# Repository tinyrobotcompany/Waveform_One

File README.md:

# Waveform One

A music-reactive LED display using an ESP32-S3, INMP441 microphone and 64×32
HUB75 panel. The current working prototype connects the panel directly to the
ESP32-S3. The ESP32-P4 touchscreen controller selects visual styles over USB,
joins the user's home Wi-Fi and hosts the local phone remote.

Migration to the Waveshare ESP32-P4-WIFI6-Touch-LCD-7B display controller is
under development. Display, touch, home Wi-Fi setup, the phone remote and S3
style control are working. Native music recognition has host/reference
verification and awaits physical P4 acceptance. The working
ESP32-S3 audio and HUB75 engine remains intact during this migration.

- [Wiring, firmware programs and build instructions](firmware/esp32/README.md)
- [ESP32-P4 display bring-up and wiring](firmware/esp32/p4_display/README.md)
- [ESP32-P4 controller architecture decision](docs/architecture/0001-esp32-p4-display-controller.md)
- [Contributing and local tests](CONTRIBUTING.md)
- [Release notes](CHANGELOG.md)
- [Over-the-air updates: development and production](pi/updater/README.md)
- [CI and releases](docs/delivery.md)
- [Pi setup and visual-style controls](pi/README.md)

Signed releases support Pi application and ESP firmware updates on commissioned devices.
Development devices install automatically; production devices ask the user to install.
Existing factory-layout ESP boards need a one-time USB migration before OTA updates.

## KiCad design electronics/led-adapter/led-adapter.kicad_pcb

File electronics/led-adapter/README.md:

# LED adapter board

A small board (72 × 44 mm) that connects the P4 touchscreen board to the LED
panel, so the P4 can drive the panel without the ESP32-S3 and without loose
jumper wires. Every cable plugs in at both ends.

```text
P4 socket P3 ──[PH2.0 12-pin cable]── J1 ┐
                                         ├─ buffers ── J3 ──[panel's grey ribbon]── LED panel
P4 socket P1 ──[PH2.0 12-pin cable]── J2 ┘
                       5 V from the LED supply ── J4
```

| Connector | Takes |
|---|---|
| J1 | Cable to the P4's **P3** socket (GPIO2–5, 28–31, 34; 3.3 V and GND) |
| J2 | Cable to the P4's **P1** socket (GPIO49–52; GND) |
| J3 | The LED panel's own 16-pin ribbon (HUB75) |
| J4 | 5 V and GND from the LED panel's supply (screw terminal) |

The labels are printed on the board.

## In the case

The board lies flat on four floor posts (M3 heat-set inserts, 5 mm high) in
the left half, behind the screen and under the P4's two 12-pin sockets, with
J1 and J2 towards the back. `board.json` gives its position (`case_left_x`,
`case_rear_y`, `standoff_height`); the casing CAD reads it from
`placement.json`, as it does for the carrier board.

## What is on it

- **Two 74AHCT245 buffers** turn the P4's 3.3 V signals into the 5 V the
  panel expects. These are the same buffers as on the carrier board.
- **The panel stays dark unless the P4 is on.** Q1 enables the buffers only
  while the P4's 3.3 V is present. Otherwise R4 holds the panel's OE high.
  R1 does the same while the P4 starts.
- **5 V comes from the LED panel's supply** through J4. The buffers draw only
  a few mA, and the P4's 12-pin sockets carry no 5 V.

The signal map is Codex's, from
`docs/commissioning/2026-10-14-p4-led-takeover.md`:

| HUB75 | R1 | G1 | B1 | R2 | G2 | B2 | A | B | C | D | CLK | LAT | OE |
|---|---|---|---|---|---|---|---|---|---|---|---|---|---|
| P4 GPIO | 2 | 3 | 4 | 5 | 28 | 29 | 30 | 31 | 34 | 49 | 52 | 50 | 51 |

The P4's socket pins come from Waveshare's 7B schematic (P1 and P3).
`tools/netlist.py` lists them pin by pin.

## Cables to buy

- **2 × PH2.0 12-pin cables with a plug at both ends, "same direction"**
  (sometimes listed as 同向 or "forward"). 10–15 cm long.
  - "Same direction" means wire 1 goes to pin 1 at the other end. The
    "reverse" kind sends wire 1 to pin 12 and **will not work**.
  - Before plugging one in, check with a multimeter that the end wires meet the
    same-numbered pins.
- The panel's grey 16-pin ribbon, which came with the panel.
- Two short wires (red and black) from the LED supply's screw terminal to J4.

## Order from JLCPCB

```sh
python3 electronics/led-adapter/tools/export_jlc.py
```

This writes `fab/`. On jlcpcb.com, follow the carrier board's steps
(`electronics/carrier/README.md`, "Order from JLCPCB"):

1. Upload `led-adapter-gerbers.zip`. Use the defaults: 2 layers, 1.6 mm,
   quantity 5.
2. Turn on PCB Assembly, top side. J1–J4 are through-hole, so choose
   **Standard** assembly with through-hole soldering.
3. Upload `led-adapter-bom.csv` and `led-adapter-cpl.csv`. Check that every
   part is matched and in stock.
4. In the placement preview, check that each part sits the right way round.
   Compare it with KiCad's render (`kicad-cli pcb render --side top`):
   - pin 1 of U1, U2, Q1, J1, J2 and J3;
   - the wire entries of J4, which face the board's front edge (away from the
     "+5V" and "GND" text), so the wires come in from the front as the case
     expects.

   Rotate any part that is wrong in JLCPCB's preview. Revision 1 was ordered
   with J4 turned the other way, and JLCPCB was asked to turn it 180° (2026-10-20);
   these files now have it the right way round.

## Regenerate

The tools reuse the carrier board's generators (`reuse.py` points them at this
folder). Don't edit the generated files by hand. Edit `tools/netlist.py` or
`board.json` instead, then run:

```sh
python3 electronics/led-adapter/tools/gen_schematic.py
KP=/Applications/KiCad/KiCad.app/Contents/Frameworks/Python.framework/Versions/Current/bin/python3
$KP electronics/led-adapter/tools/build_board.py
$KP electronics/led-adapter/tools/route_board.py      # needs Java and Freerouting, as for the carrier
K=/Applications/KiCad/KiCad.app/Contents/MacOS/kicad-cli
$K sch erc electronics/led-adapter/led-adapter.kicad_sch
$K pcb drc --schematic-parity electronics/led-adapter/led-adapter.kicad_pcb
```

## Status

- Designed, routed and checked: no design-rule violations, nothing
  unconnected, and the board matches the schematic.
- **Not yet ordered.**
- Order it only after the jumper bench test shows the panel works from the P4
  with this signal map.

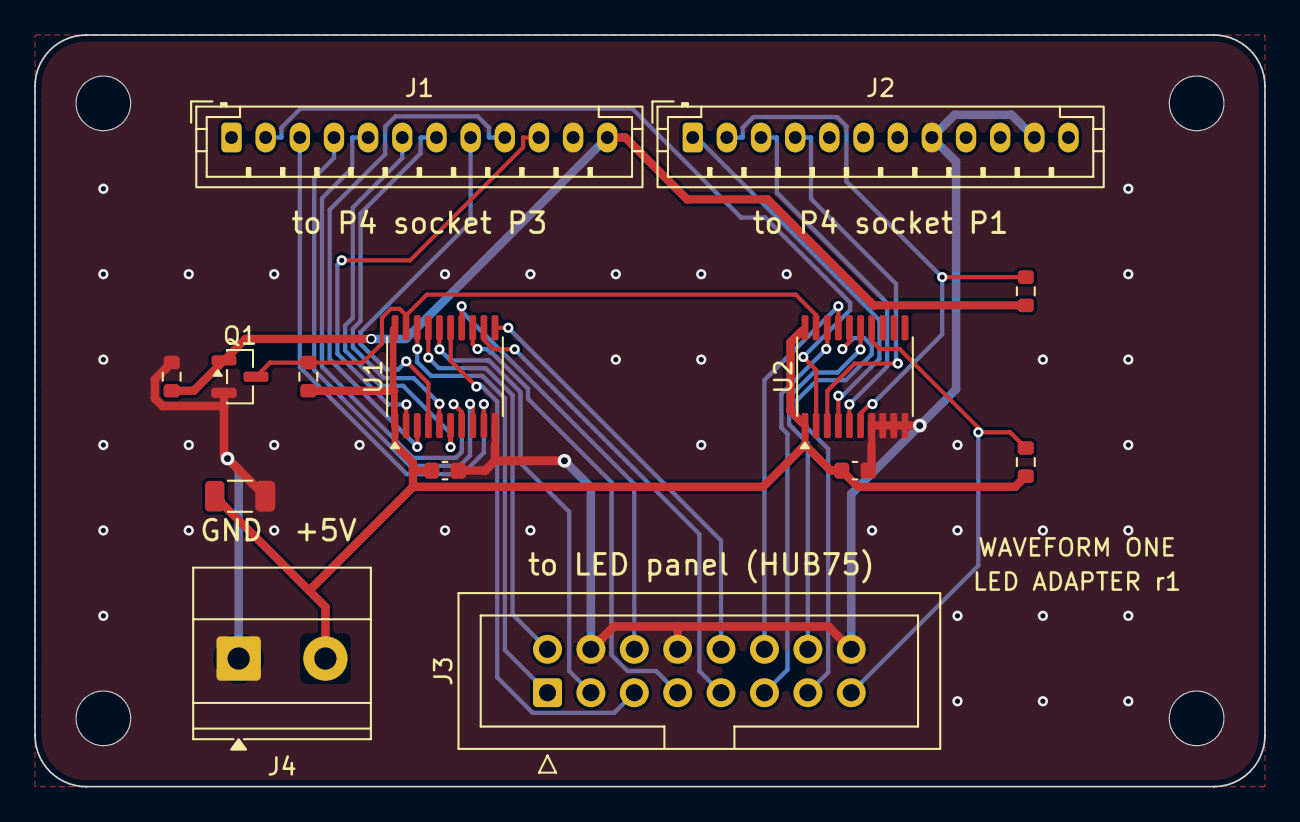
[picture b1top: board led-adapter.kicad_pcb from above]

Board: 2 copper layers, 72.0 x 44.0 mm, 18 parts (0 on the bottom side), 30 nets.

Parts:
C1, C2: 100nF; C_0603_1608Metric
C3: 22uF 10V; C_1206_3216Metric
H1, H2, H3, H4: M3; MountingHole_3.2mm_M3
J1, J2: PH2.0 12-pin; JST_PH_B12B-PH-K_1x12_P2.00mm_Vertical
J3: HUB75; IDC-Header_2x08_P2.54mm_Vertical
J4: 5V in; TerminalBlock_Phoenix_MKDS-1,5-2-5.08_1x02_P5.08mm_Horizont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
Q1: 2N7002; SOT-23
R1, R3, R4: 10k; R_0603_1608Metric
R2: 100k; R_0603_1608Metric
U1, U2: 74AHCT245; TSSOP-20_4.4x6.5mm_P0.65mm

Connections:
/+5V: C1.1, C2.1, C3.1, J4.2, R3.1, R4.1, U1.1, U1.20, U2.1, U2.20
/BUF_EN: Q1.3, R3.2, U1.19, U2.19
/GND: C1.2, C2.2, C3.2, J1.11, J2.8, J2.11, J3.4, J3.8, J3.16, J4.1, Q1.2, R2.2, U1.10, U2.7, U2.8, U2.9, U2.10
/HUB_A: J3.9, U1.12
/HUB_B: J3.10, U1.11
/HUB_B1: J3.3, U1.16
/HUB_B2: J3.7, U1.13
/HUB_C: J3.11, U2.18
/HUB_CLK: J3.13, U2.16
/HUB_D: J3.12, U2.17
/HUB_G1: J3.2, U1.17
/HUB_G2: J3.6, U1.14
/HUB_LAT: J3.14, U2.15
/HUB_OE: J3.15, R4.2, U2.14
/HUB_R1: J3.1, U1.18
/HUB_R2: J3.5, U1.15
/P4_3V3: J1.12, Q1.1, R1.1, R2.1
/P4_A: J1.4, U1.8
/P4_B: J1.3, U1.9
/P4_B1: J1.8, U1.4
/P4_B2: J1.5, U1.7
/P4_C: J1.2, U2.2
/P4_CLK: J2.1, U2.4
/P4_D: J2.4, U2.3
/P4_G1: J1.9, U1.3
/P4_G2: J1.6, U1.6
/P4_LAT: J2.3, U2.5
/P4_OE: J2.2, R1.2, U2.6
/P4_R1: J1.10, U1.2
/P4_R2: J1.7, U1.5

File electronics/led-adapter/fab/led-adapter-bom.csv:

Comment,Designator,Footprint,LCSC Part #
PH2.0 12-pin,"J1,J2",JST_PH_B12B-PH-K_1x12_P2.00mm_Vertical,C158028
10k,"R1,R3,R4",R_0603_1608Metric,C25804
2N7002,Q1,SOT-23,C8545
100k,R2,R_0603_1608Metric,C25803
74AHCT245,"U1,U2",TSSOP-20_4.4x6.5mm_P0.65mm,C173388
100nF,"C1,C2",C_0603_1608Metric,C14663
HUB75,J3,IDC-Header_2x08_P2.54mm_Vertical,C492443
5V in,J4,"TerminalBlock_Phoenix_MKDS-1,5-2-5.08_1x02_P5.08mm_Horizontal",C480516
22uF 10V,C3,C_1206_3216Metric,C12891

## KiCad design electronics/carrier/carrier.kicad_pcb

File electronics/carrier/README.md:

# Carrier board

The board inside the cabinet that carries the ESP32-S3, drives the LED panel,
connects the microphone and shares out power. See [SPEC.md](SPEC.md).

Designed in KiCad 10. Placement is generated from `board.json`, which is the
single source for the outline, mounting holes and connector positions. The
casing CAD reads the same file.

## Rebuild the board placement

```sh
/Applications/KiCad/KiCad.app/Contents/Frameworks/Python.framework/Versions/Current/bin/python3 \
    electronics/carrier/tools/build_board.py
```

## Route

```sh
/Applications/KiCad/KiCad.app/Contents/Frameworks/Python.framework/Versions/Current/bin/python3 \
    electronics/carrier/tools/route_board.py
```

Needs Java and Freerouting 2.4.1 (`FREEROUTING_JAR`). It replaces all copper:
it draws the fixed tracks in `route_board.py`, autoroutes the rest, pours
ground and stitches it, and reports what is left unconnected. Rerun it after
every `build_board.py`.

## Order from JLCPCB

```sh
python3 electronics/carrier/tools/export_jlc.py
```

This writes `fab/`: `carrier-gerbers.zip` (the board), `carrier-bom.csv`
(parts with LCSC numbers, from `LCSC` in `netlist.py`) and `carrier-cpl.csv`
(part positions). Not-fitted parts are left out. On jlcpcb.com:

1. Upload `carrier-gerbers.zip`. Keep the defaults: 2 layers, 1.6 mm,
   1 oz copper, HASL lead-free (or ENIG), quantity 5.
2. Turn on PCB Assembly: top side, assemble 5 boards. The through-hole
   connectors (J1, J4, J5, J6) need Standard assembly with through-hole
   soldering, not Economic.
3. Upload `carrier-bom.csv` and `carrier-cpl.csv`. Check every part is
   matched and in stock.
4. In the placement preview, check each polarised part sits the right way
   round: pin 1 of U1, U4, U5, U6, U7 and J7; the stripe of D1; the green LED
   D2; the + of C1; and that each connector faces the board edge it should.
   JLCPCB's part models can be rotated from KiCad's; rotate any that are
   wrong there.

## Check and preview

```sh
K=/Applications/KiCad/KiCad.app/Contents/MacOS/kicad-cli
$K pcb drc --severity-all -o /tmp/carrier-drc.txt electronics/carrier/carrier.kicad_pcb
$K pcb render --side top -o /tmp/carrier-top.png electronics/carrier/carrier.kicad_pcb
```

## Design source

`tools/netlist.py` holds the circuit: every part, value, footprint and pin net.
Two generators read it:

- `tools/gen_schematic.py` writes `carrier.kicad_sch`. Any Python 3.9+ runs it.
- `tools/build_board.py` writes `carrier.kicad_pcb`, with every pad on its net,
  and `placement.json`. It needs KiCad's Python.

Do not edit the generated files by hand. Change `netlist.py`, `board.json` or
the fixed copper in `route_board.py` and regenerate:

```sh
python3 electronics/carrier/tools/gen_schematic.py
KP=/Applications/KiCad/KiCad.app/Contents/Frameworks/Python.framework/Versions/Current/bin/python3
$KP electronics/carrier/tools/build_board.py
$KP electronics/carrier/tools/route_board.py
K=/Applications/KiCad/KiCad.app/Contents/MacOS/kicad-cli
$K sch erc electronics/carrier/carrier.kicad_sch
$K pcb drc --schematic-parity electronics/carrier/carrier.kicad_pcb
```

## Status

Revision 1 is placed and routed.

- Schematic: passes the electrical rules check. The only warnings are the
  three intentional ties of unused buffer inputs to ground.
- Board: matches the schematic exactly, and passes the design-rule check with
  no errors and nothing unconnected. Four warnings remain: the silkscreen
  outlines of the USB-A socket (J4) and the LED power terminal (J6) overhang
  the board edge, as those connectors do by design. A fifth flags that the
  S3 module's footprint differs from KiCad's library: its ground-pad holes
  are drilled 0.3 mm instead of 0.2 mm, so every hole on the board is a
  standard drill size at JLCPCB.
- Chip resistor and capacitor references are left off the silkscreen (too
  dense); they remain on the fabrication layer.
- The USB-C power parts are marked do-not-populate. Their layout is complete
  but provisional; see SPEC.md before fitting them.

Library warnings in `kicad-cli` mean KiCad's global library tables are not set
up yet. Opening KiCad once creates them.

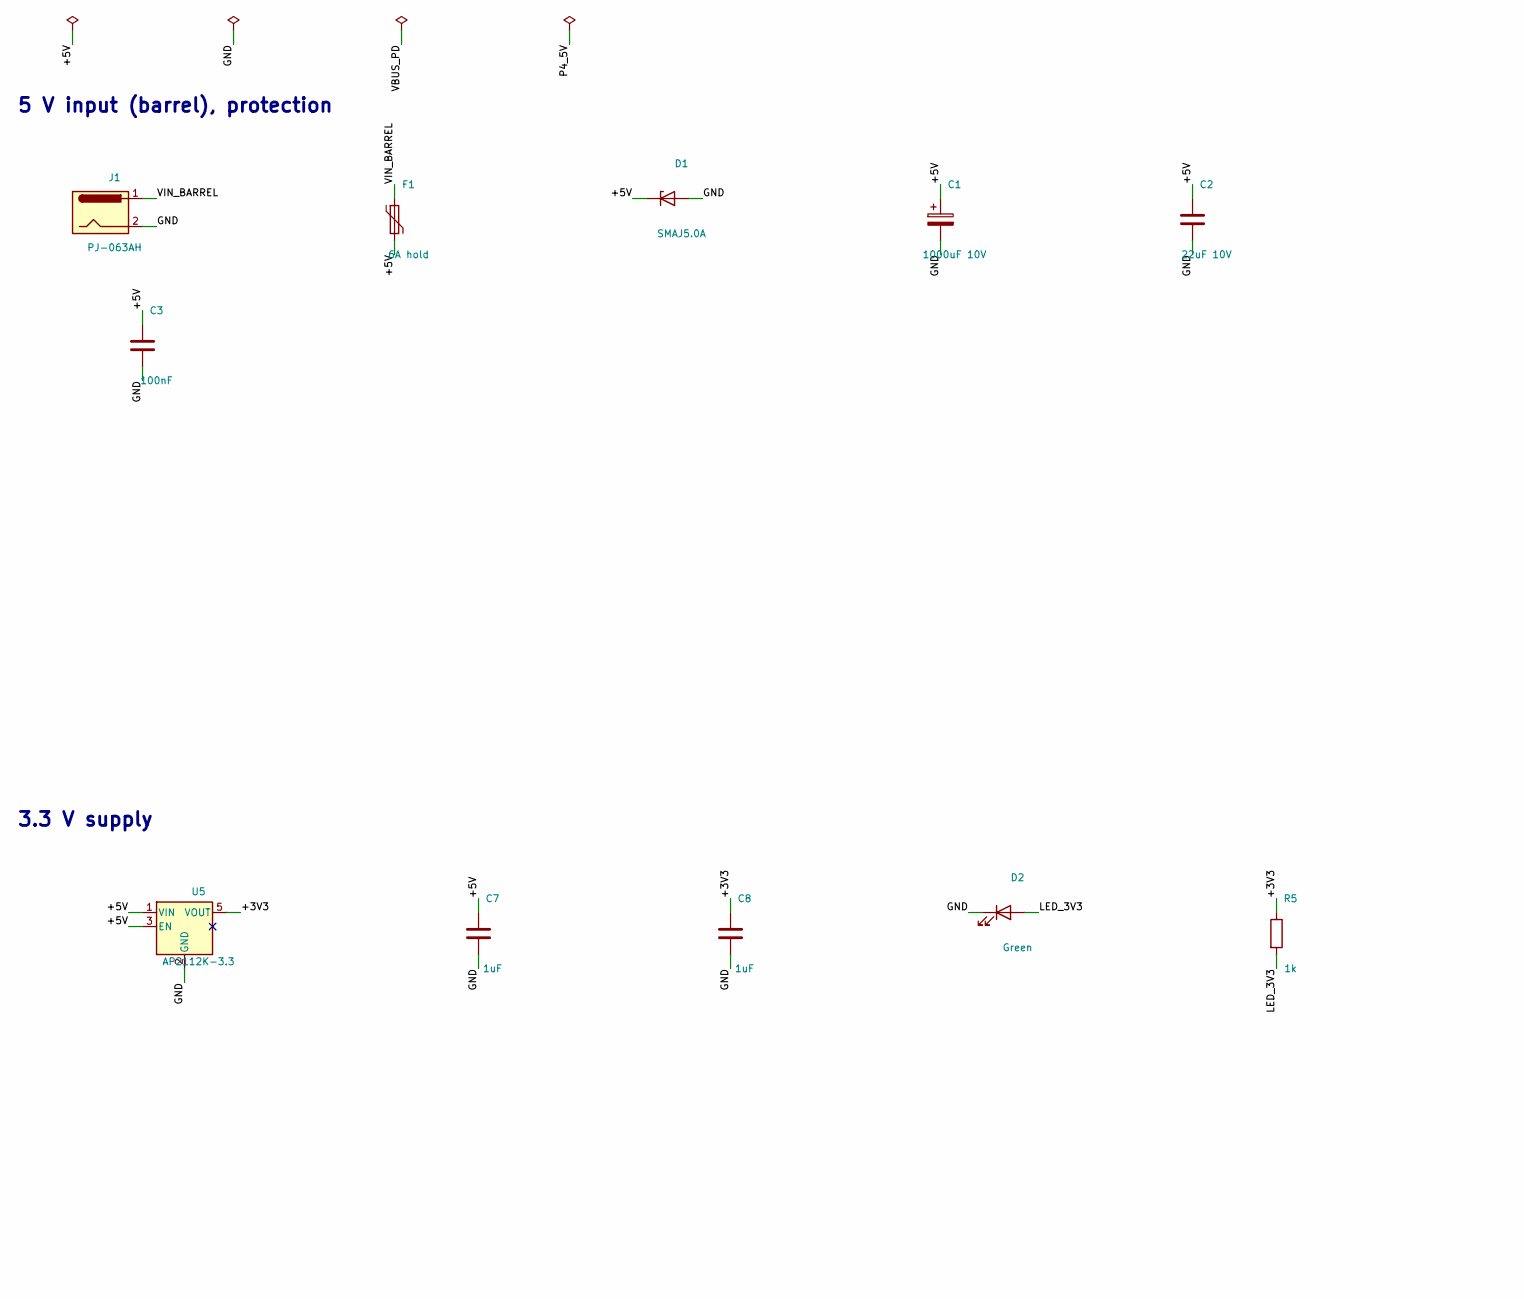
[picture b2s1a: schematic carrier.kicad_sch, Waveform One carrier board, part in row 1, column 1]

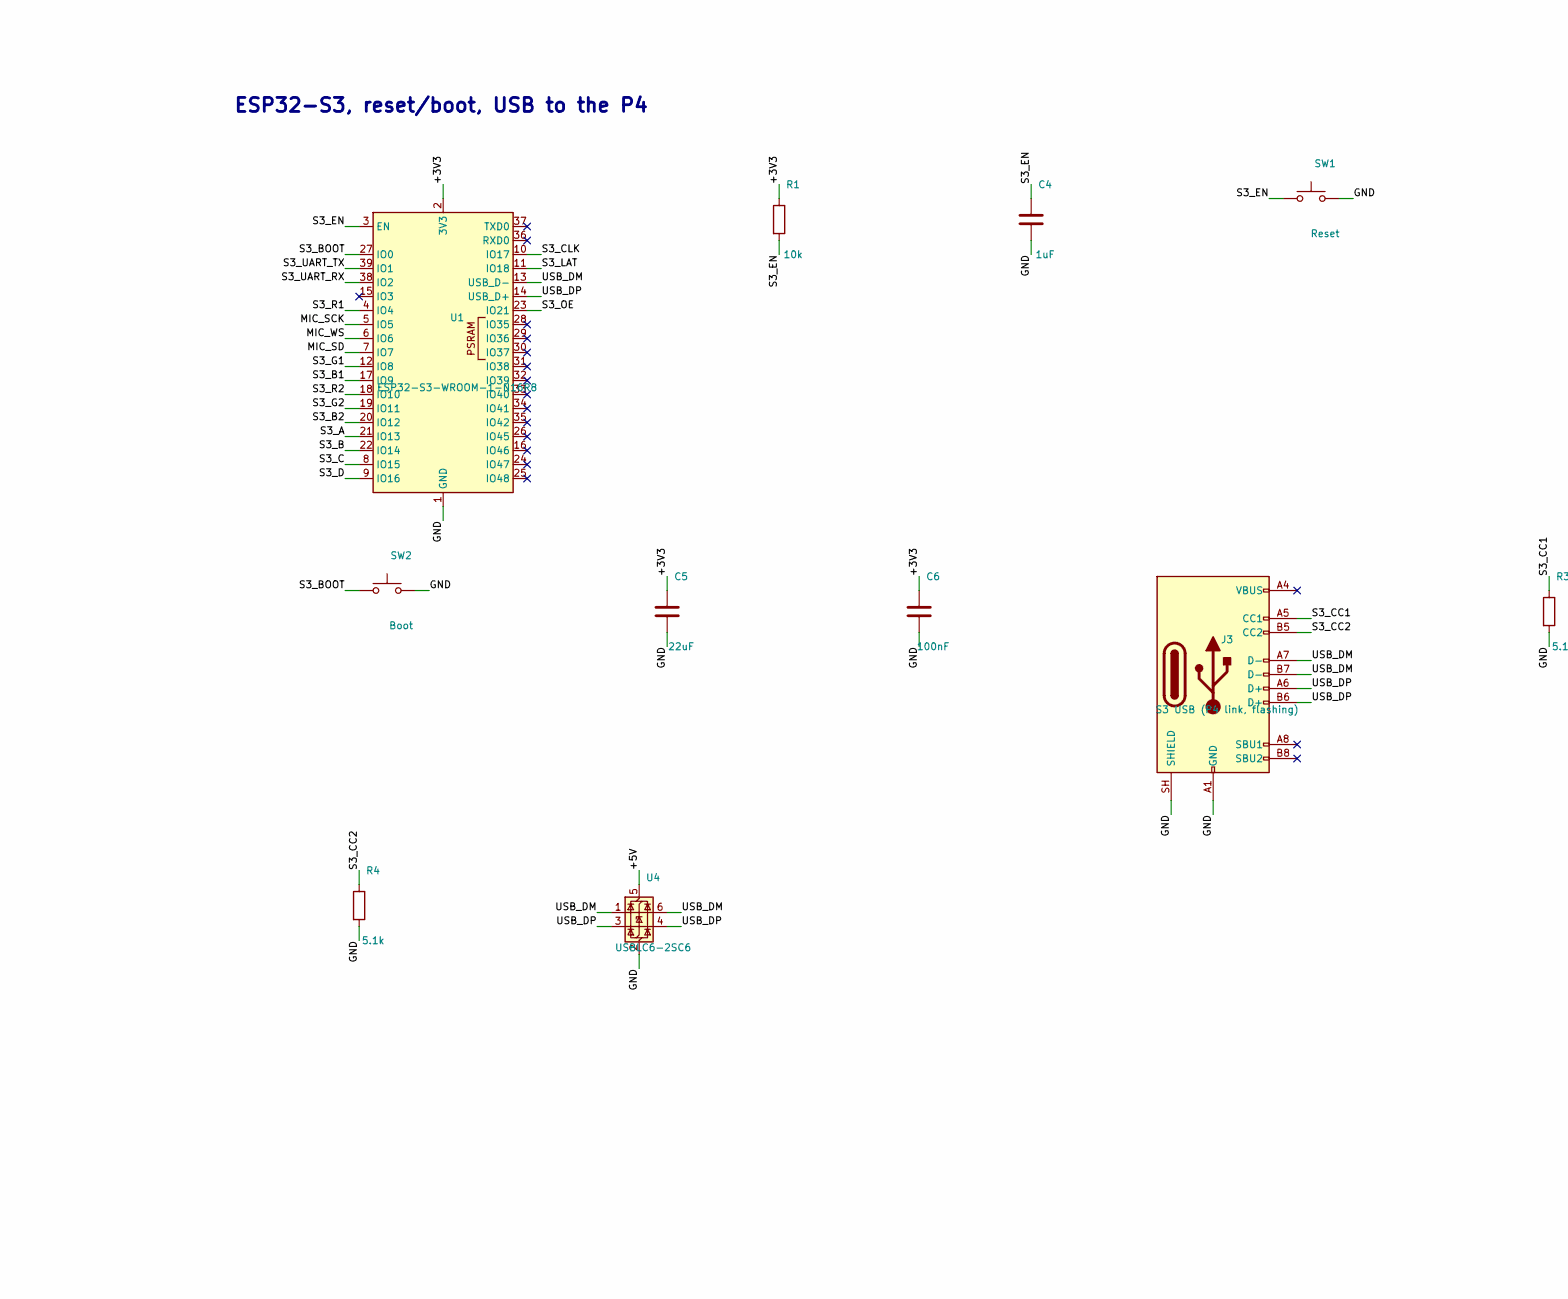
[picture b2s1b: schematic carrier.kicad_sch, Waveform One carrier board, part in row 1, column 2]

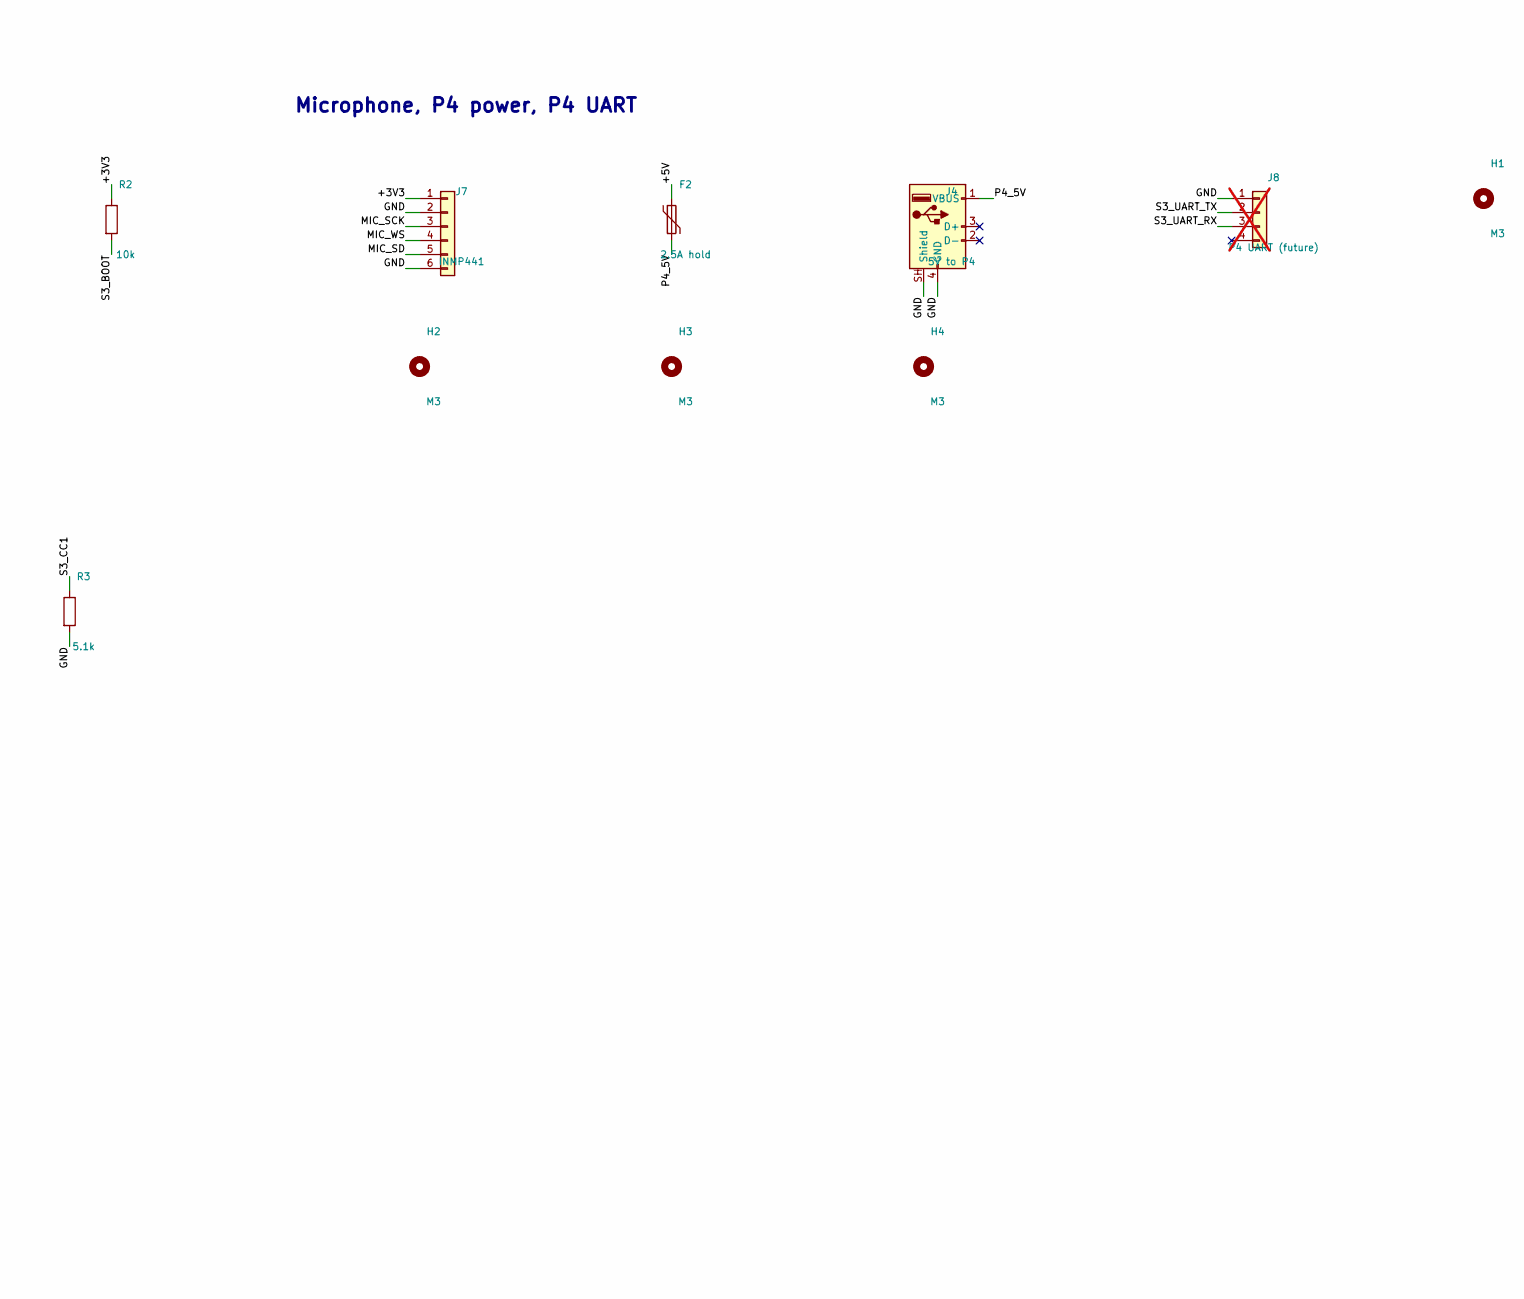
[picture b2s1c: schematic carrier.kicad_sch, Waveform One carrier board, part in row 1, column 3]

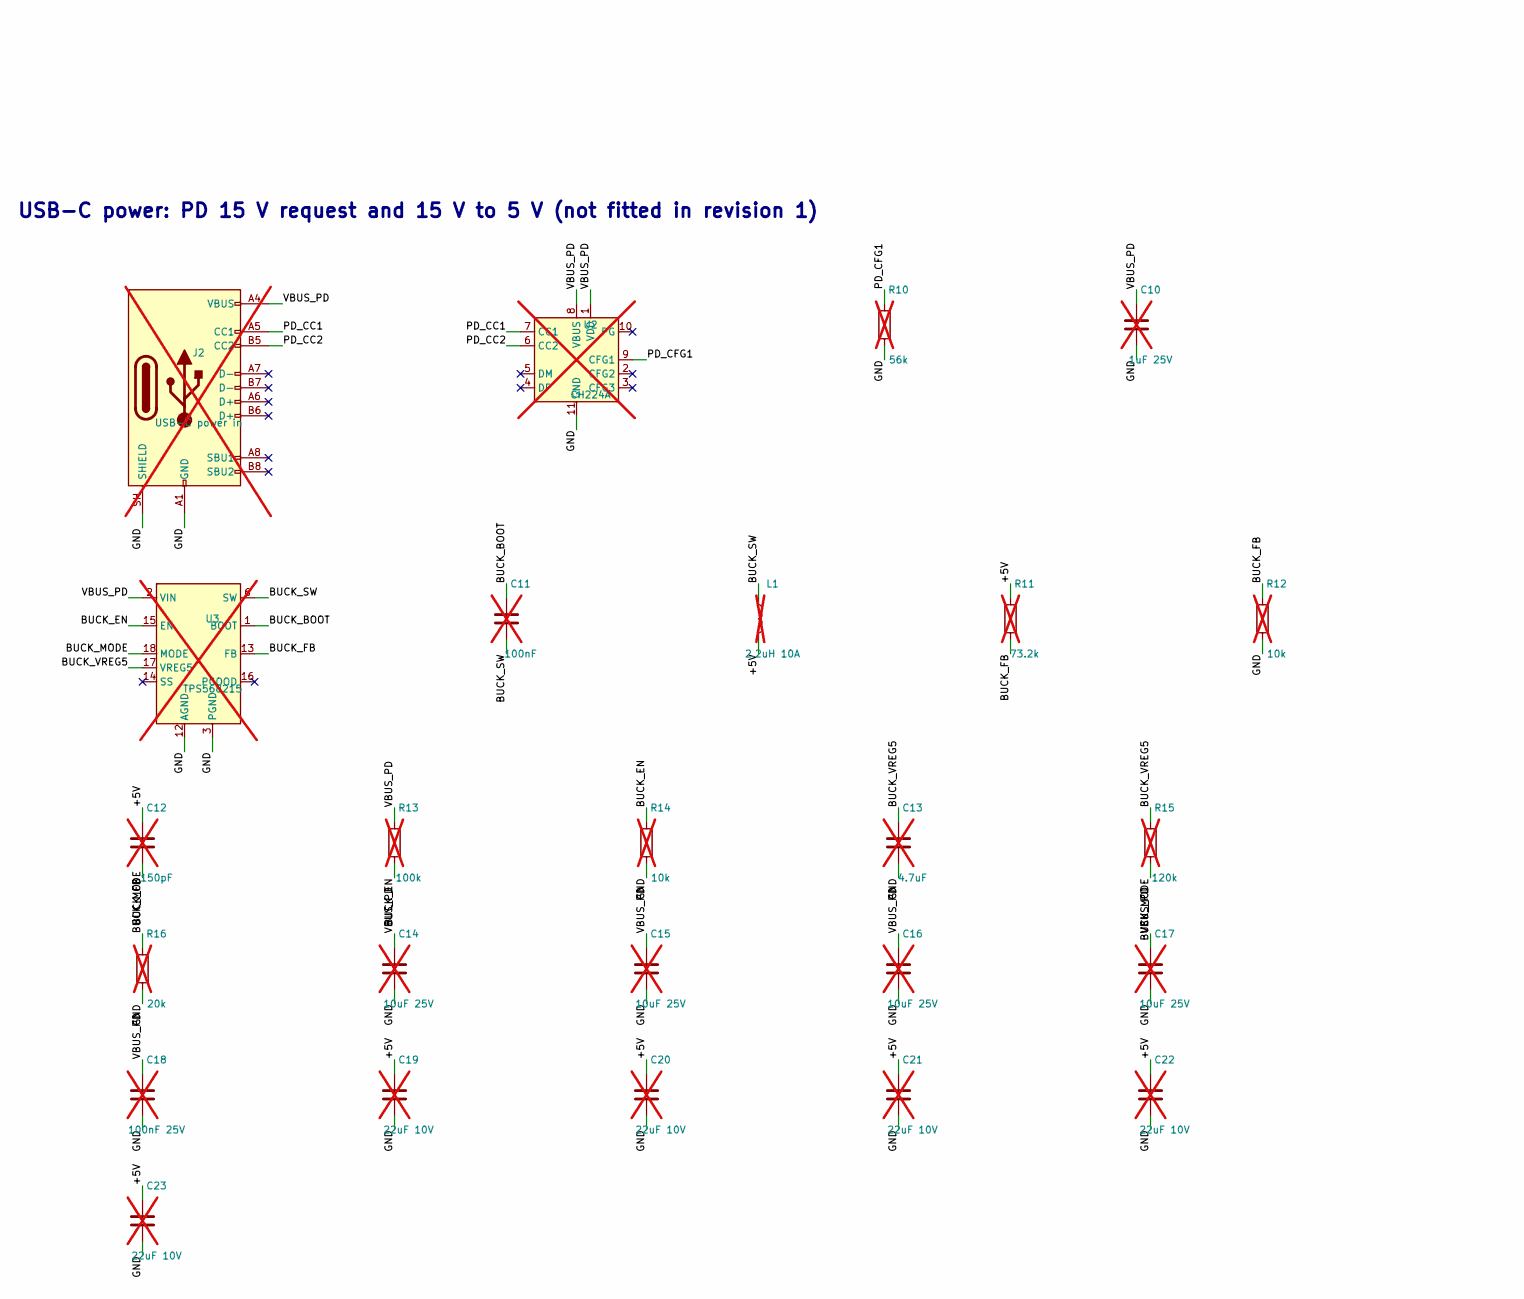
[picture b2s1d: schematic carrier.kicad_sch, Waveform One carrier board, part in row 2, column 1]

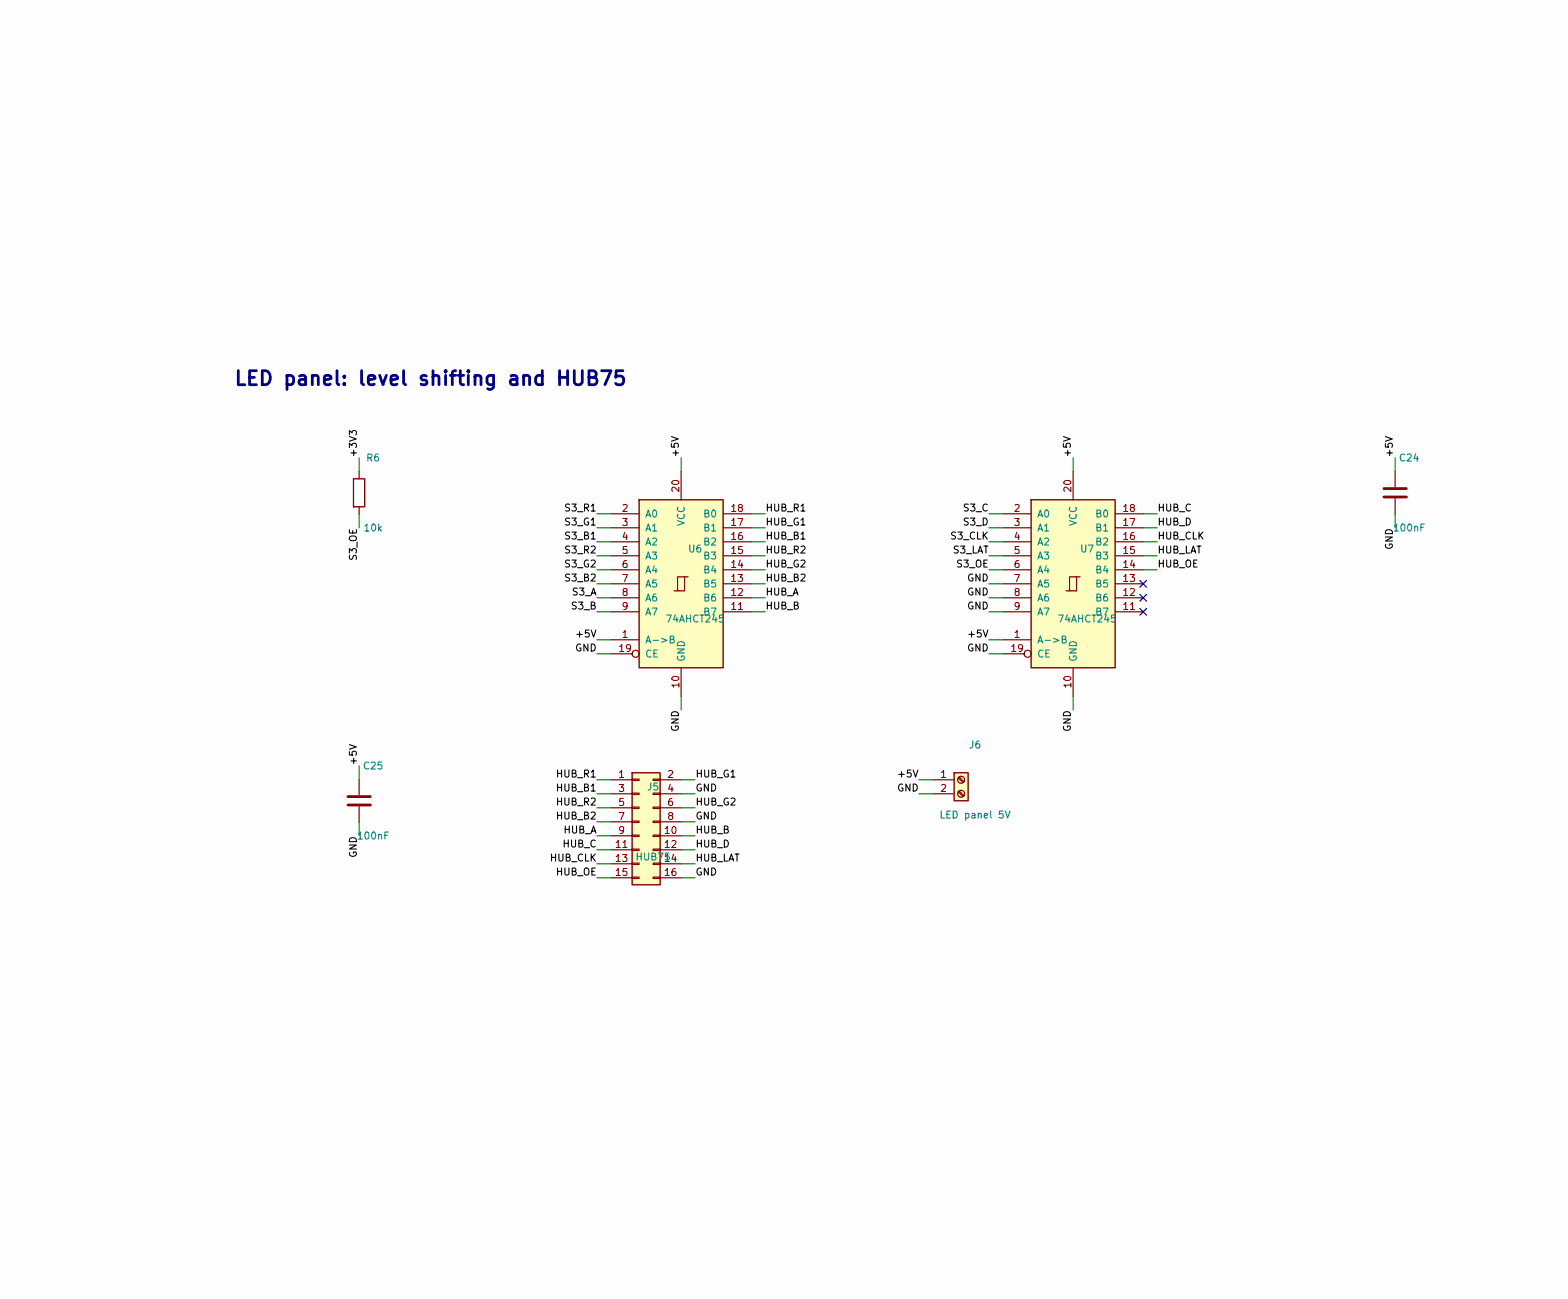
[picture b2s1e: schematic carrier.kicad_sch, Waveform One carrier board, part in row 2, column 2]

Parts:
C1: 1000uF 10V; CP_Elec_10x10.5
C2: 22uF 10V; C_1206_3216Metric
C3, C6, C24, C25: 100nF; C_0603_1608Metric
C4, C7, C8: 1uF; C_0603_1608Metric
C5: 22uF; C_1206_3216Metric
C10: 1uF 25V; C_0805_2012Metric; not fitted
C11: 100nF; C_0603_1608Metric; not fitted
C12: 150pF; C_0603_1608Metric; not fitted
C13: 4.7uF; C_0805_2012Metric; not fitted
C14, C15, C16, C17: 10uF 25V; C_1206_3216Metric; not fitted
C18: 100nF 25V; C_0603_1608Metric; not fitted
C19, C20, C21, C22, C23: 22uF 10V; C_1206_3216Metric; not fitted
D1: SMAJ5.0A; D_SMA
D2: Green; LED_0603_1608Metric
F1: 6A hold; Fuse_2920_7451Metric
F2: 2.5A hold; Fuse_1812_4532Metric
H1, H2, H3, H4: M3; MountingHole_3.2mm_M3
J1: PJ-063AH; BarrelJack_CUI_PJ-063AH_Horizontal
J2: USB-C power in; USB_C_Receptacle_HRO_TYPE-C-31-M-12; not fitted
J3: S3 USB (P4 link, flashing); USB_C_Receptacle_GCT_USB4105-xx-A_16P_TopMnt_Horizontal
J4: 5V to P4; USB_A_Molex_67643_Horizontal
J5: HUB75; IDC-Header_2x08_P2.54mm_Vertical
J6: LED panel 5V; TerminalBlock_Phoenix_MKDS-1,5-2-5.08_1x02_P5.08mm_Horizont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
J7: INMP441; JST_GH_BM06B-GHS-TBT_1x06-1MP_P1.25mm_Vertical
J8: P4 UART (future); JST_PH_B4B-PH-K_1x04_P2.00mm_Vertical; not fitted
L1: 2.2uH 10A; L_Coilcraft_XAL7070-XXX; not fitted
R1, R2, R6: 10k; R_0603_1608Metric
R3, R4: 5.1k; R_0603_1608Metric
R5: 1k; R_0603_1608Metric
R10: 56k; R_0603_1608Metric; not fitted
R11: 73.2k; R_0603_1608Metric; not fitted
R12, R14: 10k; R_0603_1608Metric; not fitted
R13: 100k; R_0603_1608Metric; not fitted
R15: 120k; R_0603_1608Metric; not fitted
R16: 20k; R_0603_1608Metric; not fitted
SW1: Reset; SW_SPST_TL3342
SW2: Boot; SW_SPST_TL3342
U1: ESP32-S3-WROOM-1-N16R8; ESP32-S3-WROOM-1
U2: CH224A; SSOP-10-1EP_3.9x4.9mm_P1mm_EP2.1x3.3mm; not fitted
U3: TPS568215; Texas_RNN0018A; not fitted
U4: USBLC6-2SC6; SOT-23-6
U5: AP2112K-3.3; SOT-23-5
U6, U7: 74AHCT245; TSSOP-20_4.4x6.5mm_P0.65mm

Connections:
/+3V3: C5.1, C6.1, C8.1, J7.1, R1.1, R2.1, R5.1, R6.1, U1.2 (3V3), U5.5 (VOUT)
/+5V: C1.1, C2.1, C3.1, C7.1, C12.1, C19.1, C20.1, C21.1, C22.1, C23.1, C24.1, C25.1, D1.1 (K), F1.2, F2.1, J6.1, L1.2, R11.1, U4.5 (VBUS), U5.1 (VIN), U5.3 (EN), U6.1 (A->B), U6.20 (VCC), U7.1 (A->B), U7.20 (VCC)
/BUCK_BOOT: C11.1, U3.1 (BOOT)
/BUCK_EN: R13.2, R14.1, U3.15 (EN)
/BUCK_FB: C12.2, R11.2, R12.1, U3.13 (FB)
/BUCK_MODE: R15.2, R16.1, U3.18 (MODE)
/BUCK_SW: C11.2, L1.1, U3.6 (SW), U3.7 (SW)
/BUCK_VREG5: C13.1, R15.1, U3.17 (VREG5)
/GND: C1.2, C2.2, C3.2, C4.2, C5.2, C6.2, C7.2, C8.2, C10.2, C13.2, C14.2, C15.2, C16.2, C17.2, C18.2, C19.2, C20.2, C21.2, C22.2, C23.2, C24.2, C25.2, D1.2 (A), D2.1 (K), J1.2, J2.A1 (GND), J2.A12 (GND), J2.B1 (GND), J2.B12 (GND), J2.SH (SHIELD), J3.A1 (GND), J3.A12 (GND), J3.B1 (GND), J3.B12 (GND), J3.SH (SHIELD), J4.4 (GND), J4.SH (Shield), J5.4, J5.8, J5.16, J6.2, J7.2, J7.6, J8.1, R3.2, R4.2, R10.2, R12.2, R14.2, R16.2, SW1.2, SW2.2, U1.1 (GND), U1.40 (GND), U1.41 (GND), U2.11 (GND), U3.3 (PGND), U3.4 (PGND), U3.5 (PGND), U3.8 (PGND), U3.9 (PGND), U3.10 (PGND), U3.12 (AGND), U4.2 (GND), U5.2 (GND), U6.10 (GND), U6.19 (CE), U7.7 (A5), U7.8 (A6), U7.9 (A7), U7.10 (GND), U7.19 (CE)
/HUB_A: J5.9, U6.12 (B6)
/HUB_B: J5.10, U6.11 (B7)
/HUB_B1: J5.3, U6.16 (B2)
/HUB_B2: J5.7, U6.13 (B5)
/HUB_C: J5.11, U7.18 (B0)
/HUB_CLK: J5.13, U7.16 (B2)
/HUB_D: J5.12, U7.17 (B1)
/HUB_G1: J5.2, U6.17 (B1)
/HUB_G2: J5.6, U6.14 (B4)
/HUB_LAT: J5.14, U7.15 (B3)
/HUB_OE: J5.15, U7.14 (B4)
/HUB_R1: J5.1, U6.18 (B0)
/HUB_R2: J5.5, U6.15 (B3)
/LED_3V3: D2.2 (A), R5.2
/MIC_SCK: J7.3, U1.5 (IO5)
/MIC_SD: J7.5, U1.7 (IO7)
/MIC_WS: J7.4, U1.6 (IO6)
/P4_5V: F2.2, J4.1 (VBUS)
/PD_CC1: J2.A5 (CC1), U2.7 (CC1)
/PD_CC2: J2.B5 (CC2), U2.6 (CC2)
/PD_CFG1: R10.1, U2.9 (CFG1)
/S3_A: U1.21 (IO13), U6.8 (A6)
/S3_B: U1.22 (IO14), U6.9 (A7)
/S3_B1: U1.17 (IO9), U6.4 (A2)
/S3_B2: U1.20 (IO12), U6.7 (A5)
/S3_BOOT: R2.2, SW2.1, U1.27 (IO0)
/S3_C: U1.8 (IO15), U7.2 (A0)
/S3_CC1: J3.A5 (CC1), R3.1
/S3_CC2: J3.B5 (CC2), R4.1
/S3_CLK: U1.10 (IO17), U7.4 (A2)
/S3_D: U1.9 (IO16), U7.3 (A1)
/S3_EN: C4.1, R1.2, SW1.1, U1.3 (EN)
/S3_G1: U1.12 (IO8), U6.3 (A1)
/S3_G2: U1.19 (IO11), U6.6 (A4)
/S3_LAT: U1.11 (IO18), U7.5 (A3)
/S3_OE: R6.2, U1.23 (IO21), U7.6 (A4)
/S3_R1: U1.4 (IO4), U6.2 (A0)
/S3_R2: U1.18 (IO10), U6.5 (A3)
/S3_UART_RX: J8.3, U1.38 (IO2)
/S3_UART_TX: J8.2, U1.39 (IO1)
/USB_DM: J3.A7 (D-), J3.B7 (D-), U1.13 (USB_D-), U4.1 (I/O1), U4.6 (I/O1)
/USB_DP: J3.A6 (D+), J3.B6 (D+), U1.14 (USB_D+), U4.3 (I/O2), U4.4 (I/O2)
/VBUS_PD: C10.1, C14.1, C15.1, C16.1, C17.1, C18.1, J2.A4 (VBUS), J2.A9 (VBUS), J2.B4 (VBUS), J2.B9 (VBUS), R13.1, U2.1 (VDD), U2.8 (VBUS), U3.2 (VIN), U3.11 (VIN)
/VIN_BARREL: F1.1, J1.1

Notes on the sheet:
5 V input (barrel), protection
3.3 V supply
USB-C power: PD 15 V request and 15 V to 5 V (not fitted in revision 1)
ESP32-S3, reset/boot, USB to the P4
LED panel: level shifting and HUB75
Microphone, P4 power, P4 UART

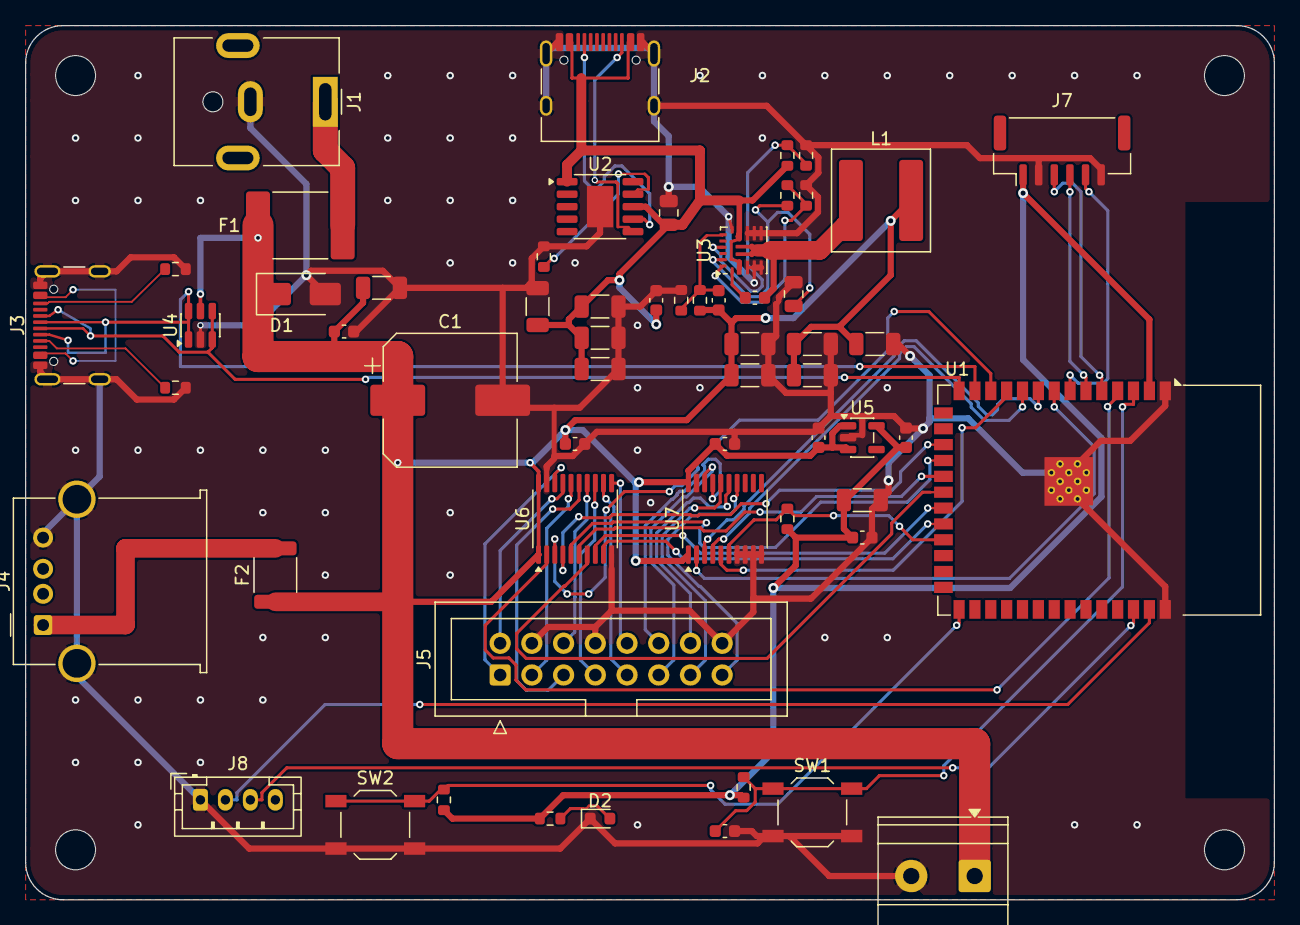
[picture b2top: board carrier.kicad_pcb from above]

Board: 2 copper layers, 100.0 x 70.0 mm, 63 parts (0 on the bottom side), 53 nets.

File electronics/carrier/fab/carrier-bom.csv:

Comment,Designator,Footprint,LCSC Part #
PJ-063AH,J1,BarrelJack_CUI_PJ-063AH_Horizontal,C22434582
6A hold,F1,Fuse_2920_7451Metric,C49318508
SMAJ5.0A,D1,D_SMA,C78401
1000uF 10V,C1,CP_Elec_10x10.5,C165632
22uF 10V,"C2,C5",C_1206_3216Metric,C12891
100nF,"C3,C6,C24,C25",C_0603_1608Metric,C14663
AP2112K-3.3,U5,SOT-23-5,C51118
1uF,"C7,C8,C4",C_0603_1608Metric,C15849
Green,D2,LED_0603_1608Metric,C12624
1k,R5,R_0603_1608Metric,C21190
ESP32-S3-WROOM-1-N16R8,U1,ESP32-S3-WROOM-1,C2913202
10k,"R1,R2,R6",R_0603_1608Metric,C25804
Reset,"SW1,SW2",SW_SPST_TL3342,C2886898
"S3 USB (P4 link, flashing)",J3,USB_C_Receptacle_GCT_USB4105-xx-A_16P_TopMnt_Horizontal,C5184243
5.1k,"R3,R4",R_0603_1608Metric,C23186
USBLC6-2SC6,U4,SOT-23-6,C7519
74AHCT245,"U6,U7",TSSOP-20_4.4x6.5mm_P0.65mm,C173388
HUB75,J5,IDC-Header_2x08_P2.54mm_Vertical,C492443
LED panel 5V,J6,"TerminalBlock_Phoenix_MKDS-1,5-2-5.08_1x02_P5.08mm_Horizontal",C480516
INMP441,J7,JST_GH_BM06B-GHS-TBT_1x06-1MP_P1.25mm_Vertical,C225122
2.5A hold,F2,Fuse_1812_4532Metric,C19078727
5V to P4,J4,USB_A_Molex_67643_Horizontal,C2798029
